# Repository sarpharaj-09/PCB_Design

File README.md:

# 🔧 PCB Design Portfolio

<p align="center">
  <strong>A collection of my PCB designs, custom footprints, and electronic hardware projects.</strong>
</p>

---

## 📌 About This Repository

Welcome to my **PCB Design Repository**!

This repository is my personal collection of printed circuit board (PCB) designs, custom footprints, and related electronic design resources. Whenever I design a new PCB, create a footprint, or work on a hardware design, I upload the relevant files here to document my progress and maintain a collection of my work.

The repository will continue to grow as I explore new electronic components, develop circuit boards, and improve my PCB design skills.

## 🎯 Repository Goals

* 📐 Store and organize my PCB designs.
* 🔩 Create and maintain custom PCB footprints.
* 🔌 Document electronic circuit and hardware projects.
* 🧩 Build a reusable collection of design resources.
* 📚 Track my progress in electronics and PCB development.
* 🚀 Share my designs and learn from the engineering community.

## 📂 What's Inside?

This repository may include the following resources as projects are developed.

| Resource            | Description                                              |
| ------------------- | -------------------------------------------------------- |
| PCB Designs         | Custom printed circuit board layouts                     |
| Footprints          | Custom component footprints for PCB layouts              |
| Schematics          | Circuit diagrams and electrical connections              |
| 3D PCB Models       | Three-dimensional board previews and component placement |
| Design Files        | Editable source files from PCB design software           |
| Manufacturing Files | Gerber files and drill files when available              |
| Documentation       | Images, notes, and project-specific information          |

*The files available for each project depend on the design and its development stage.*

## 🛠️ Tools and Technologies

My hardware design workflow may involve:

* **PCB Design Software:** KiCad, EasyEDA, or other electronic design automation (EDA) tools.
* **Circuit Design:** Schematic capture and component selection.
* **Footprint Design:** Creating and modifying component land patterns.
* **PCB Layout:** Component placement, copper routing, and board organization.
* **3D Visualization:** Inspecting board layouts and component placement.

The specific software used for each design depends on the project.

## 🗂️ Project Collection

This repository contains individual PCB design projects and related resources.

### Current Projects

* [ESP32-WROOM-32 Development Board](./ESPWROOM32_dev/) — Custom development board PCB design.

More projects, footprints, and design resources will be added as I create them.

## 🔍 How to Explore the Repository

1. Browse the project folders.
2. Open the available schematic and PCB layout files using compatible EDA software.
3. Review the included images and 3D renders, if available.
4. Inspect custom footprints and their dimensions before using them in another design.
5. Check for manufacturing files if you intend to fabricate a board.

## 📐 PCB Design Workflow

My general PCB design workflow includes:

1. **Planning** — Identify the circuit requirements and select components.
2. **Schematic Design** — Create the circuit diagram and establish electrical connections.
3. **Footprint Creation** — Create or verify component footprints against datasheets.
4. **PCB Layout** — Arrange components and route the electrical connections.
5. **Design Verification** — Review dimensions, clearances, connectivity, and design-rule-check results.
6. **3D Inspection** — Inspect component placement and mechanical alignment.
7. **Manufacturing Preparation** — Generate fabrication outputs when the design is ready.

Not every project will have completed all these stages.

## ⚠️ Important Notes

* Always verify footprint dimensions and pin assignments against the manufacturer's datasheet.
* Review the schematic and PCB design before manufacturing.
* Do not assume a design has been physically tested unless its documentation explicitly confirms it.
* Manufacturing files may not be available for every project.
* Check the applicable license and attribution requirements before reusing or redistributing design files.

## 🔮 Future Plans

As this repository grows, I plan to:

* Add more custom PCB designs.
* Develop reusable footprints for electronic components.
* Include more schematic diagrams and 3D PCB renders.
* Document component selection and design decisions.
* Add Gerber files and bills of materials where appropriate.
* Improve project organization and documentation.

## 🤝 Feedback and Contributions

Feedback, suggestions, and technical discussions are welcome.

If you find an issue with a design or have suggestions for improvement, feel free to open a GitHub issue. Contributions and constructive feedback can help improve the quality and usability of these designs.

## 👨‍💻 Author

**Sarpharaj**

* GitHub: [@sarpharaj-09](https://github.com/sarpharaj-09)
* Repository: [PCB_Design](https://github.com/sarpharaj-09/PCB_Design)

## 📄 License

Unless a license is specified in the repository, the designs should not be assumed to be available for unrestricted reuse or redistribution. A suitable license can be added to clarify the permissions for using and modifying the hardware designs.

---

<p align="center">
  <strong>Design. Build. Learn. Improve.</strong>
</p>

<p align="center">
  <i>A growing collection of my PCB designs and footprint development work.</i>
</p>

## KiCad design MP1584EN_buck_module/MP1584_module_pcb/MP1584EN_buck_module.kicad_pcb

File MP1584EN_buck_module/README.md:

# MP1584EN Adjustable Buck Converter

An adjustable DC-DC step-down converter PCB based on the MP1584EN switching regulator. The design includes input and output terminals, an adjustable output-voltage control, and a compact layout.

## Design specifications

The schematic lists the following design targets:

| Parameter | Design target |
| --- | --- |
| Regulator | MP1584EN |
| Input voltage | 4.5 V to 28 V |
| Adjustable output voltage | 0.8 V to 25 V |
| Output current | Up to 3 A, subject to input/output conditions and thermal limits |
| Output adjustment | RV1 potentiometer |

These are schematic specifications, not verified performance measurements. Check the regulator datasheet and validate the assembled board under your intended load before use.

## Board views

### Front

### Back

### Copper footprint views

| Front copper | Back copper |
| --- | --- |
|  |  |

The board is marked with input (`IN+`, `IN-`) and output (`OUT+`, `OUT-`) connections.

## Schematic

The output can be made fixed by removing potentiometer RV1 and installing a resistor at R5. The schematic gives the relationship:

```text
R5 (kΩ) = 50.25 × (VOUT - 0.8)
```

Confirm the resulting voltage and resistor value against the schematic and regulator datasheet before powering the board.

## Project files

| Path | Description |
| --- | --- |
| `MP1584_module_pcb/MP1584EN_buck_module.kicad_sch` | Editable circuit schematic |
| `MP1584_module_pcb/MP1584EN_buck_module.kicad_pcb` | Editable PCB layout |
| `MP1584_module_pcb/MP1584EN_buck_module.kicad_pro` | KiCad project settings |
| `MP1584_module_pcb/Gerber_file/` | Gerber fabrication layers |
| `media/image/` | Board renders, schematic image, and footprint views |

Open the KiCad project in a compatible KiCad version to inspect or edit the design. Review the schematic, board layout, footprints, clearances, and design-rule-check results before fabrication. The included Gerber files should also be checked against the final PCB layout.

## Safety and use

This design can involve potentially high currents. Use a suitable current-limited power source, verify input polarity and output voltage before connecting a load, and account for regulator and component heating. No assembled-board testing is documented here.

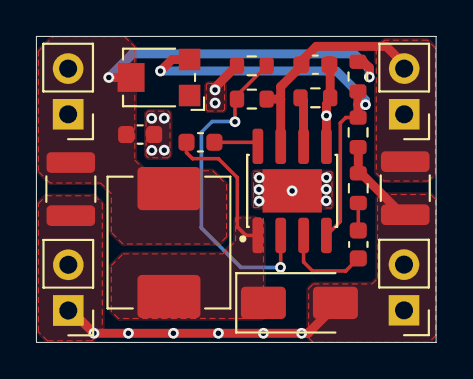
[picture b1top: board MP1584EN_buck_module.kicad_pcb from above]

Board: 2 copper layers, 22.2 x 17.0 mm, 20 parts (0 on the bottom side), 10 nets.

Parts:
C1: 10uF 50V; C_1210_3225Metric
C2, C3, C5: 100nF; C_0603_1608Metric
C4: 100pF; C_0603_1608Metric
C6: 22uF 50V; C_1210_3225Metric
D1: D; D_SMA
IN+1: TestPoint; PinHeader_1x02_P2.54mm_Vertical
IN-1: TestPoint; PinHeader_1x02_P2.54mm_Vertical
L1: 15uH; L_TechFuse_SL0630
OUT+1: TestPoint; PinHeader_1x02_P2.54mm_Vertical
OUT-1: TestPoint; PinHeader_1x02_P2.54mm_Vertical
R1, R3, R4: 100K; R_0603_1608Metric
R2: 24.9K; R_0603_1608Metric
R5: 261K(For Vout=6V); R_0603_1608Metric
R6: 40.2K; R_0603_1608Metric
RV1: R_Potentiometer; Potentiometer_Bourns_TC33X_Vertical
U1: MP1584EN; SOIC127P600X170-9N

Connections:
FB: R5.1 (A), R6.1, RV1.3, U1.4 (FB)
GND: C1.2, C2.2, C5.2, C6.2, D1.2 (A), IN-1.1 (1_1), IN-1.2, OUT-1.1 (1_1), OUT-1.2, R2.2, R3.2, R4.2, R6.2, U1.5 (GND), U1.9 (GND)
unnamed: C4.2, R4.1
unnamed: C3.1, D1.1 (K), L1.1, U1.1 (SW)
unnamed: C5.1, C6.1, L1.2, OUT+1.1 (1_1), OUT+1.2, R5.2 (B), RV1.2
unnamed: C3.2, U1.8 (BST)
unnamed: C4.1, U1.3 (COMP)
unnamed: R1.2, R2.1, U1.2 (EN)
unnamed: R3.1, U1.6 (FREQ)
unnamed: C1.1, C2.1, IN+1.1 (1_1), IN+1.2, R1.1, U1.7 (VIN)

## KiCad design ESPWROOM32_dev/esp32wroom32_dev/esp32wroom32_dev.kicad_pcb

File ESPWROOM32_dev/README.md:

# ESP32-WROOM-32 Development Board — PCB Design

<p align="center">
  <strong>Custom PCB Design for Embedded Systems and IoT Applications</strong>
</p>

---

## 📌 Overview

This project presents a custom-designed **ESP32-WROOM-32 development board PCB** for embedded systems, electronics prototyping, and Internet of Things (IoT) applications.

The project includes PCB design visualizations, the circuit schematic, and a video demonstration. The board is designed around the ESP32-WROOM-32 module, which provides wireless connectivity and processing capabilities for a wide range of embedded applications.

This repository serves as a reference for understanding, reviewing, and further developing the PCB design.

## ✨ Features

* ESP32-WROOM-32-based development board.
* Wi-Fi and Bluetooth connectivity supported by the ESP32 module.
* Custom printed circuit board (PCB) layout.
* Circuit schematic for reviewing electrical connections.
* 3D PCB visualization for inspecting component placement.
* PCB design suitable for embedded systems and IoT prototyping.
* Design assets organized for convenient reference.

*Note: Actual board interfaces, power circuitry, and supported peripherals depend on the implemented schematic and component selection.*

---

## 📸 PCB Design Gallery

### 1. 3D Front View

The 3D front view provides a visual representation of the PCB and its component placement.

### 2. 3D Back View

The back view helps inspect the reverse side of the PCB and its layout.

### 3. PCB Layout

The PCB layout illustrates the board design, component arrangement, and routing.

### 4. Circuit Schematic

The schematic provides an overview of the circuit connections and electronic components.

---

## 🎥 Project Video Demonstration

Watch the PCB design demonstration to see the board visualization and design presentation.

<p align="center">
  
</p>

<p align="center">
  <a href="./media/videos/pcb_design_demo.mp4">
    <strong>▶️ Watch the PCB Design Demo</strong>
  </a>
</p>

**Video location:** [`media/videos/pcb_design_demo.mp4`](./media/videos/pcb_design_demo.mp4)

*Click the thumbnail or the link above to open the video.*

---

## 🛠️ Hardware and Design Tools

| Item                   | Description                         |
| ---------------------- | ----------------------------------- |
| Microcontroller module | ESP32-WROOM-32                      |
| Hardware type          | Custom PCB development board        |
| Design documentation   | PCB layout and circuit schematic    |
| Visualization          | 3D PCB renders                      |
| Main application       | Embedded systems and IoT            |
| Design software        | Refer to the original project files |

The PCB design software and additional hardware specifications should be documented according to the actual project files.

---

## 📂 Repository Structure

The project media files are organized as follows:

```text
ESPWROOM32_dev/
├── README.md
└── media/
    ├── images/
    │   ├── pcb_3d_front.png
    │   ├── pcb_3d_back.png
    │   ├── pcb_layout.png
    │   ├── schematic.png
    │   └── video_thumbnail.png
    └── videos/
        └── pcb_design_demo.mp4
```

### File Descriptions

| File                  | Purpose                                          |
| --------------------- | ------------------------------------------------ |
| `pcb_3d_front.png`    | Front-side 3D PCB visualization                  |
| `pcb_3d_back.png`     | Back-side 3D PCB visualization                   |
| `pcb_layout.png`      | PCB layout and routing view                      |
| `schematic.png`       | Circuit schematic                                |
| `video_thumbnail.png` | Preview image linking to the demonstration video |
| `pcb_design_demo.mp4` | PCB design demonstration video                   |

---

## 🚀 Getting Started

### 1. Clone the Repository

Open a terminal and run:

```bash
git clone https://github.com/sarpharaj-09/PCB_Design.git
```

### 2. Navigate to the Project Directory

```bash
cd PCB_Design/ESPWROOM32_dev
```

### 3. Review the Design

* Open the images to inspect the PCB and schematic.
* Watch the demonstration video.
* Review the original schematic and PCB design files, if included in the repository.

### 4. Modify or Manufacture the PCB

If the editable design files are available, open them in the compatible PCB design software to inspect or modify the board.

Before manufacturing, verify the schematic, footprints, board dimensions, electrical clearances, routing, and design-rule-check results. Generate the required fabrication files using the appropriate design software.

---

## 💡 Potential Applications

The ESP32-WROOM-32 platform is suitable for projects such as:

* Internet of Things (IoT) devices.
* Wireless sensor monitoring.
* Home automation systems.
* Remote monitoring and control.
* Embedded systems prototyping.
* Wi-Fi and Bluetooth-enabled electronics.
* Educational electronics and PCB design projects.

These are potential applications of the platform, not necessarily implemented or tested features of this specific board.

---

## 🔍 Future Improvements

Possible future improvements to the project include:

* Adding detailed component specifications and a bill of materials (BOM).
* Including the editable schematic and PCB source files.
* Providing Gerber and drill files for fabrication.
* Documenting the power supply and USB programming interface, if implemented.
* Adding board dimensions and connector pinout diagrams.
* Including hardware testing results and assembly instructions.
* Providing a demonstration of the assembled board.

---

## 🤝 Contributions

Suggestions and improvements are welcome.

To contribute:

1. Fork this repository.
2. Create a branch for your changes.
3. Make and commit your modifications.
4. Submit a pull request with a description of the improvements.

---

## 📄 License

Please check the repository's license file for the applicable usage and redistribution terms.

If no license is included, the project should not be assumed to be open for unrestricted reuse or redistribution. Consider adding an appropriate license if you intend to share the design for reuse.

---

## 👨‍💻 Author

**Sarpharaj**

GitHub: [@sarpharaj-09](https://github.com/sarpharaj-09)

Project: [PCB_Design — ESPWROOM32_dev](https://github.com/sarpharaj-09/PCB_Design/tree/main/ESPWROOM32_dev)

---

<p align="center">
  <strong>Designed for embedded systems, electronics prototyping, and IoT development.</strong>
</p>

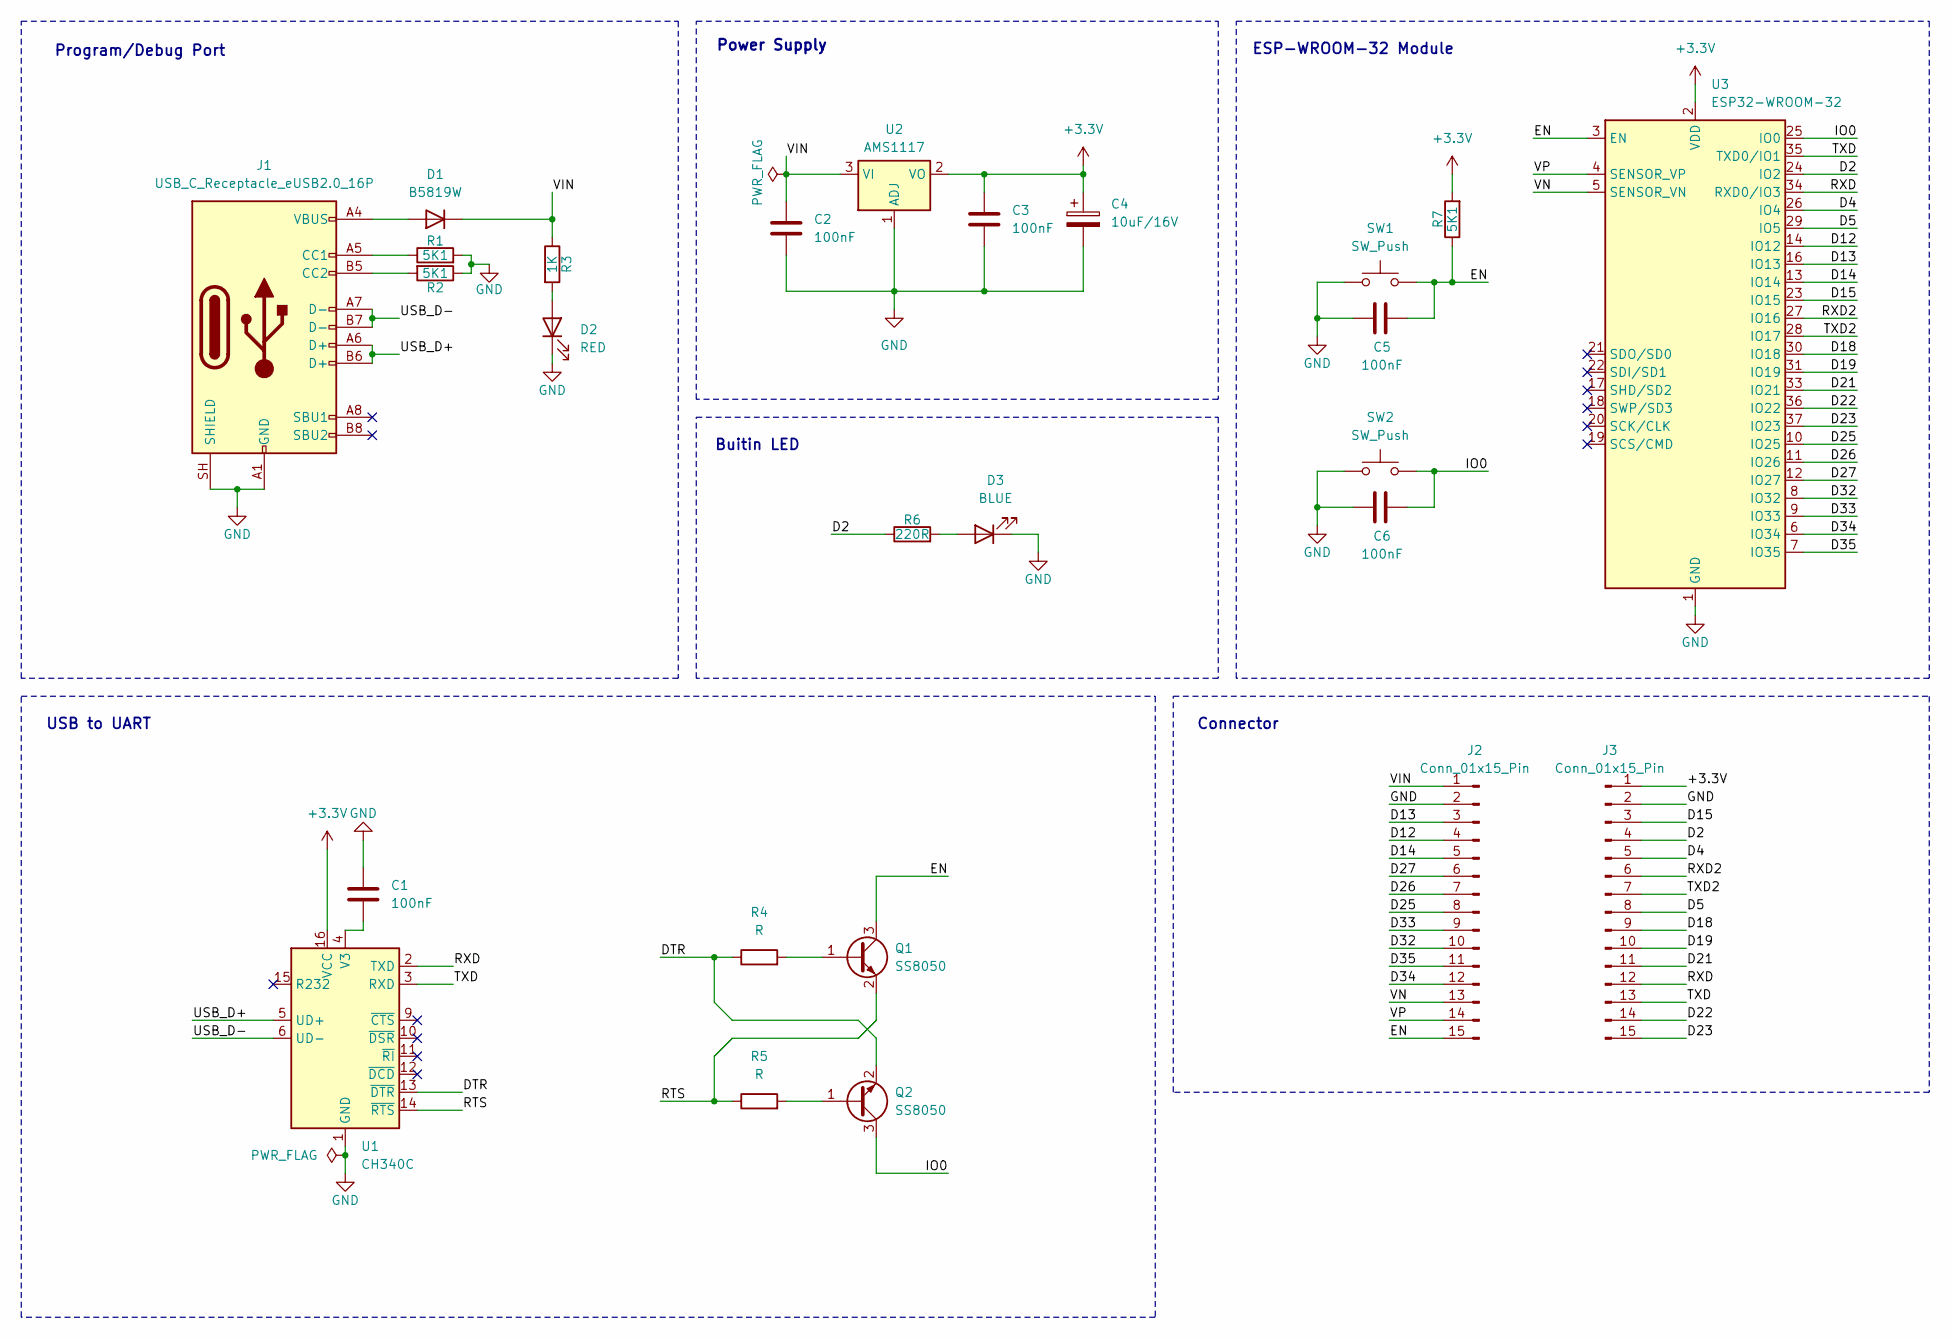
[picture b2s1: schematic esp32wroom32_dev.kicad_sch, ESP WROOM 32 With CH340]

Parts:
C1, C2, C3, C5, C6: 100nF; C_0603_1608Metric
C4: 10uF/16V; CP_EIA-3216-10_Kemet-I
D1: B5819W; D_SOD-123
D2: RED; LED_0603_1608Metric
D3: BLUE; LED_0603_1608Metric
J1: USB_C_Receptacle_eUSB2.0_16P; USB_C_Receptacle_HRO_TYPE-C-31-M-12
J2, J3: Conn_01x15_Pin; PinHeader_1x15_P2.54mm_Vertical
Q1, Q2: SS8050; SOT-23
R1, R2, R7: 5K1; R_0603_1608Metric
R3: 1K; R_0603_1608Metric
R4, R5: R; R_0603_1608Metric
R6: 220R; R_0603_1608Metric
SW1, SW2: SW_Push; SW_Push_SPST_NO_Alps_SKRK
U1: CH340C; SOIC-16_3.9x9.9mm_P1.27mm
U2: AMS1117; SOT-223-3_TabPin2
U3: ESP32-WROOM-32

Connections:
+3.3V: C3.1, C4.1, J3.1, R7.2, U1.16 (VCC), U2.2 (VO), U3.2 (VDD)
/D2: J3.4, R6.1, U3.24 (IO2)
/D4: J3.5, U3.26 (IO4)
/D5: J3.8, U3.29 (IO5)
/D12: J2.4, U3.14 (IO12)
/D13: J2.3, U3.16 (IO13)
/D14: J2.5, U3.13 (IO14)
/D15: J3.3, U3.23 (IO15)
/D18: J3.9, U3.30 (IO18)
/D19: J3.10, U3.31 (IO19)
/D21: J3.11, U3.33 (IO21)
/D22: J3.14, U3.36 (IO22)
/D23: J3.15, U3.37 (IO23)
/D25: J2.8, U3.10 (IO25)
/D26: J2.7, U3.11 (IO26)
/D27: J2.6, U3.12 (IO27)
/D32: J2.10, U3.8 (IO32)
/D33: J2.9, U3.9 (IO33)
/D34: J2.12, U3.6 (IO34)
/D35: J2.11, U3.7 (IO35)
/DTR: Q2.2 (E), R4.1, U1.13 (~DTR)
/EN: C5.2, J2.15, Q1.3 (C), R7.1, SW1.2, U3.3 (EN)
/IO0: C6.2, Q2.3 (C), SW2.2, U3.25 (IO0)
/RTS: Q1.2 (E), R5.1, U1.14 (~RTS)
/RXD: J3.12, U1.2 (TXD), U3.34 (RXD0/IO3)
/RXD2: J3.6, U3.27 (IO16)
/TXD: J3.13, U1.3 (RXD), U3.35 (TXD0/IO1)
/TXD2: J3.7, U3.28 (IO17)
/USB_D+: J1.A6 (D+), J1.B6 (D+), U1.5 (UD+)
/USB_D-: J1.A7 (D-), J1.B7 (D-), U1.6 (UD-)
/VIN: C2.1, D1.1 (K), J2.1, R3.1, U2.3 (VI)
/VN: J2.13, U3.5 (SENSOR_VN)
/VP: J2.14, U3.4 (SENSOR_VP)
GND: C1.1, C2.2, C3.2, C4.2, C5.1, C6.1, D2.1 (K), D3.1 (K), J1.A1 (GND), J1.A12 (GND), J1.B1 (GND), J1.B12 (GND), J1.SH (SHIELD), J2.2, J3.2, R1.2, R2.1, SW1.1, SW2.1, U1.1 (GND), U2.1 (ADJ), U3.1 (GND), U3.15 (GND), U3.38 (GND), U3.39 (GND)
unnamed: D1.2 (A), J1.A4 (VBUS), J1.A9 (VBUS), J1.B4 (VBUS), J1.B9 (VBUS)
unnamed: D2.2 (A), R3.2
unnamed: D3.2 (A), R6.2
unnamed: J1.A5 (CC1), R1.1
unnamed: J1.B5 (CC2), R2.2
unnamed: Q1.1 (B), R4.2
unnamed: Q2.1 (B), R5.2
unnamed: C1.2, U1.4 (V3)

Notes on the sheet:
Program/Debug Port
Connector
USB to UART
ESP-WROOM-32 Module
Buitin LED
Power Supply

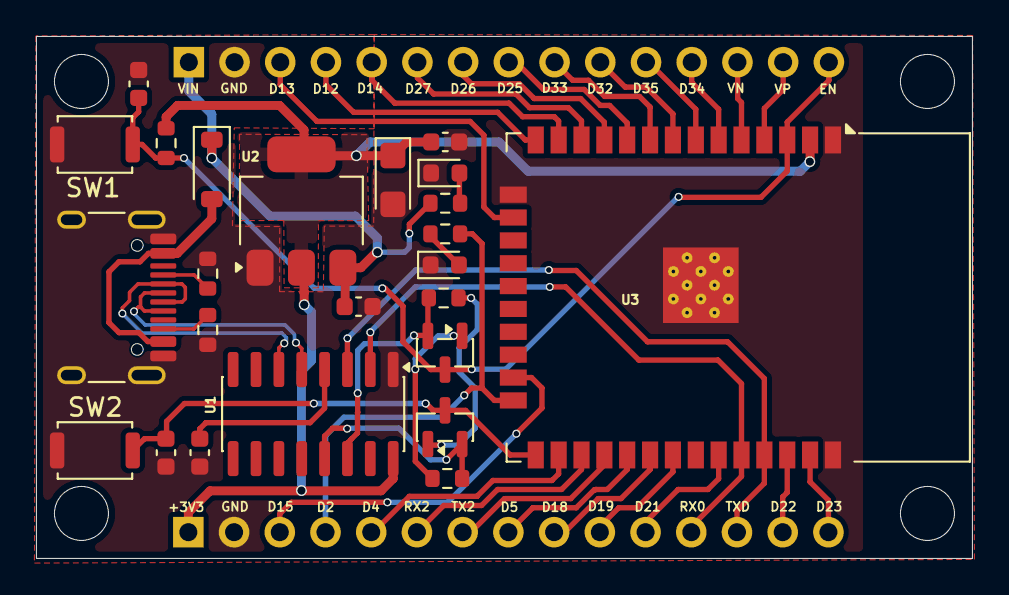
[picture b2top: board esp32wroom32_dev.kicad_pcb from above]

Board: 2 copper layers, 52.0 x 29.0 mm, 26 parts (0 on the bottom side), 42 nets.

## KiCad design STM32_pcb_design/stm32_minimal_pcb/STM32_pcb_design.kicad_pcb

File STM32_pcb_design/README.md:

# ESP32-WROOM-32 Development Board — PCB Design

<p align="center">
  <strong>Custom PCB Design for Embedded Systems and IoT Applications</strong>
</p>

---

## 📌 Overview

This project presents a custom-designed **ESP32-WROOM-32 development board PCB** for embedded systems, electronics prototyping, and Internet of Things (IoT) applications.

The project includes PCB design visualizations, the circuit schematic, and a video demonstration. The board is designed around the ESP32-WROOM-32 module, which provides wireless connectivity and processing capabilities for a wide range of embedded applications.

This repository serves as a reference for understanding, reviewing, and further developing the PCB design.

## ✨ Features

* ESP32-WROOM-32-based development board.
* Wi-Fi and Bluetooth connectivity supported by the ESP32 module.
* Custom printed circuit board (PCB) layout.
* Circuit schematic for reviewing electrical connections.
* 3D PCB visualization for inspecting component placement.
* PCB design suitable for embedded systems and IoT prototyping.
* Design assets organized for convenient reference.

*Note: Actual board interfaces, power circuitry, and supported peripherals depend on the implemented schematic and component selection.*

---

## 📸 PCB Design Gallery

### 1. 3D Front View

The 3D front view provides a visual representation of the PCB and its component placement.

### 2. 3D Back View

The back view helps inspect the reverse side of the PCB and its layout.

### 3. PCB Layout

The PCB layout illustrates the board design, component arrangement, and routing.

### 4. Circuit Schematic

The schematic provides an overview of the circuit connections and electronic components.

---

## 🎥 Project Video Demonstration

Watch the PCB design demonstration to see the board visualization and design presentation.

<p align="center">
  <a href="./media/videos/pcb_design_demo.mp4">
    ▶️ <strong>Watch the PCB Design Demo (MP4)</strong>
  </a>
</p>

**Video location:** [`media/videos/pcb_design_demo.mp4`](./media/videos/pcb_design_demo.mp4)

*Click the link above to open the video.*

---

## 🛠️ Hardware and Design Tools

| Item                   | Description                         |
| ---------------------- | ----------------------------------- |
| Microcontroller module | ESP32-WROOM-32                      |
| Hardware type          | Custom PCB development board        |
| Design documentation   | PCB layout and circuit schematic    |
| Visualization          | 3D PCB renders                      |
| Main application       | Embedded systems and IoT            |
| Design software        | Refer to the original project files |

The PCB design software and additional hardware specifications should be documented according to the actual project files.

---

## 📂 Repository Structure

The project media files are organized as follows:

```text
ESPWROOM32_dev/
├── README.md
└── media/
    ├── images/
    │   ├── pcb_3d_front.png
    │   ├── pcb_3d_back.png
    │   ├── pcb_layout.png
    │   └── schematic.png
    └── videos/
        └── pcb_design_demo.mp4
```

### File Descriptions

| File                  | Purpose                         |
| --------------------- | ------------------------------- |
| `pcb_3d_front.png`    | Front-side 3D PCB visualization |
| `pcb_3d_back.png`     | Back-side 3D PCB visualization  |
| `pcb_layout.png`      | PCB layout and routing view     |
| `schematic.png`       | Circuit schematic               |
| `pcb_design_demo.mp4` | PCB design demonstration video  |

---

## 🚀 Getting Started

### 1. Clone the Repository

Open a terminal and run:

```bash
git clone https://github.com/sarpharaj-09/PCB_Design.git
```

### 2. Navigate to the Project Directory

```bash
cd PCB_Design/ESPWROOM32_dev
```

### 3. Review the Design

* Open the images to inspect the PCB and schematic.
* Watch the demonstration video.
* Review the original schematic and PCB design files, if included in the repository.

### 4. Modify or Manufacture the PCB

If the editable design files are available, open them in the compatible PCB design software to inspect or modify the board.

Before manufacturing, verify the schematic, footprints, board dimensions, electrical clearances, routing, and design-rule-check results. Generate the required fabrication files using the appropriate design software.

---

## 💡 Potential Applications

The ESP32-WROOM-32 platform is suitable for projects such as:

* Internet of Things (IoT) devices.
* Wireless sensor monitoring.
* Home automation systems.
* Remote monitoring and control.
* Embedded systems prototyping.
* Wi-Fi and Bluetooth-enabled electronics.
* Educational electronics and PCB design projects.

These are potential applications of the platform, not necessarily implemented or tested features of this specific board.

---

## 🔍 Future Improvements

Possible future improvements to the project include:

* Adding detailed component specifications and a bill of materials (BOM).
* Including the editable schematic and PCB source files.
* Providing Gerber and drill files for fabrication.
* Documenting the power supply and USB programming interface, if implemented.
* Adding board dimensions and connector pinout diagrams.
* Including hardware testing results and assembly instructions.
* Providing a demonstration of the assembled board.

---

## 🤝 Contributions

Suggestions and improvements are welcome.

To contribute:

1. Fork this repository.
2. Create a branch for your changes.
3. Make and commit your modifications.
4. Submit a pull request with a description of the improvements.

---

## 📄 License

Please check the repository's license file for the applicable usage and redistribution terms.

If no license is included, the project should not be assumed to be open for unrestricted reuse or redistribution. Consider adding an appropriate license if you intend to share the design for reuse.

---

## 👨‍💻 Author

**Sarpharaj**

GitHub: [@sarpharaj-09](https://github.com/sarpharaj-09)

Project: [PCB_Design — ESPWROOM32_dev](https://github.com/sarpharaj-09/PCB_Design/tree/main/ESPWROOM32_dev)

---

<p align="center">
  <strong>Designed for embedded systems, electronics prototyping, and IoT development.</strong>
</p>

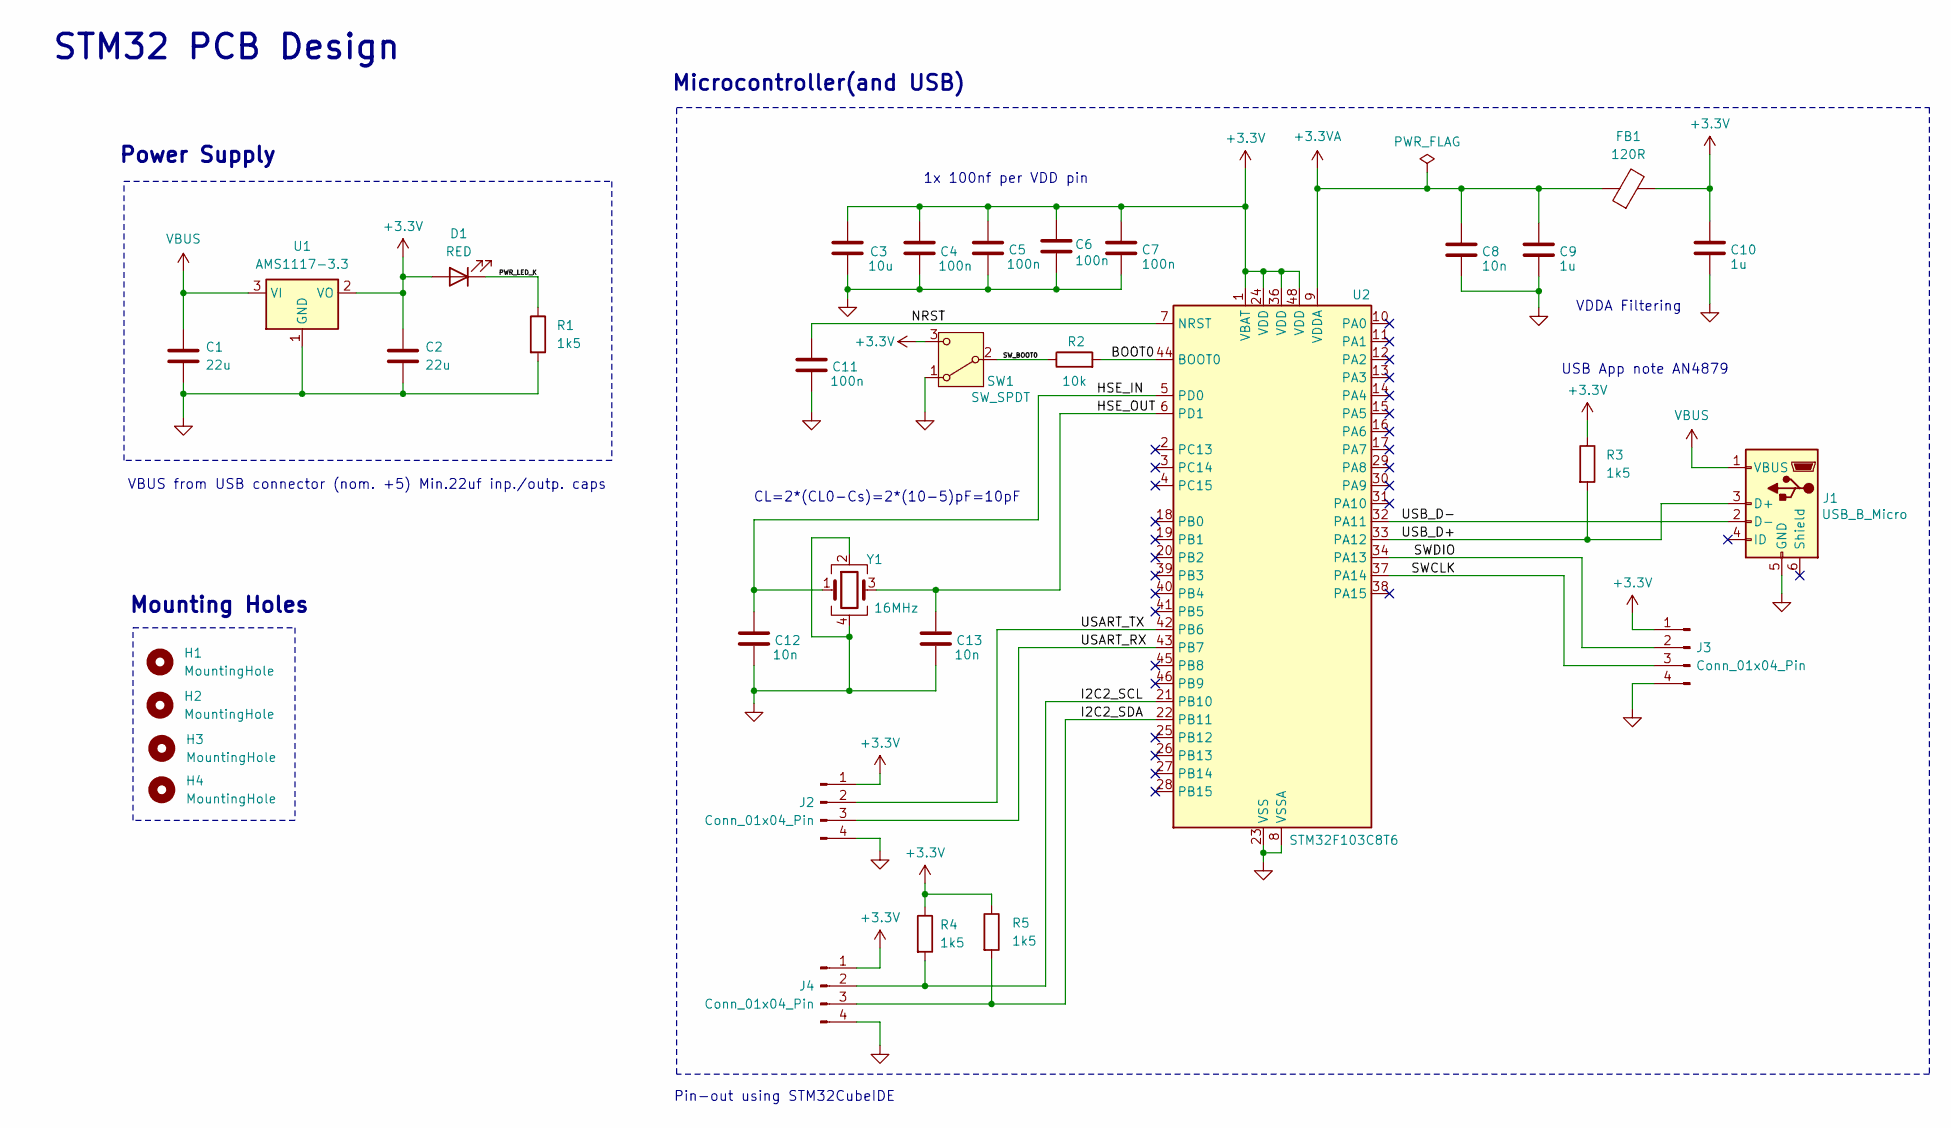
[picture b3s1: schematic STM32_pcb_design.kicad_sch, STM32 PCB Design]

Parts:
C1, C2: 22u; C_0805_2012Metric
C3: 10u; C_0603_1608Metric
C4, C5, C6, C7, C11: 100n; C_0402_1005Metric
C8, C12, C13: 10n; C_0402_1005Metric
C9, C10: 1u; C_0402_1005Metric
D1: RED; LED_0603_1608Metric
FB1: 120R; L_0603_1608Metric
H1, H2, H3, H4: MountingHole; MountingHole_2.2mm_M2
J1: USB_B_Micro; USB_Micro-B_Wuerth_629105150521
J2, J3, J4: Conn_01x04_Pin; PinHeader_1x04_P2.54mm_Vertical
R1, R3, R4, R5: 1k5; R_0402_1005Metric
R2: 10k; R_0402_1005Metric
SW1: SW_SPDT; SW_SPDT_PCM12
U1: AMS1117-3.3; SOT-223-3_TabPin2
U2: STM32F103C8T6; LQFP-48_7x7mm_P0.5mm
Y1: 16MHz; Crystal_SMD_3225-4Pin_3.2x2.5mm

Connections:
+3.3V: C2.1, C3.1, C4.1, C5.1, C6.1, C7.1, C10.1, D1.2 (A), FB1.2, J2.1, J3.1, J4.1, R3.1, R4.1, R5.1, SW1.3 (C), U1.2 (VO), U2.1 (VBAT), U2.24 (VDD), U2.36 (VDD), U2.48 (VDD)
+3.3VA: C8.1, C9.1, FB1.1, U2.9 (VDDA)
/BOOT0: R2.2, U2.44 (BOOT0)
/HSE_IN: C12.1, U2.5 (PD0), Y1.1
/HSE_OUT: C13.1, U2.6 (PD1), Y1.3
/I2C2_SCL: J4.2, R4.2, U2.21 (PB10)
/I2C2_SDA: J4.3, R5.2, U2.22 (PB11)
/NRST: C11.1, U2.7 (NRST)
/PWR_LED_K: D1.1 (K), R1.1
/SWCLK: J3.3, U2.37 (PA14)
/SWDIO: J3.2, U2.34 (PA13)
/SW_BOOT0: R2.1, SW1.2 (B)
/USART_RX: J2.3, U2.43 (PB7)
/USART_TX: J2.2, U2.42 (PB6)
/USB_D+: J1.3 (D+), R3.2, U2.33 (PA12)
/USB_D-: J1.2 (D-), U2.32 (PA11)
GND: C1.2, C2.2, C3.2, C4.2, C5.2, C6.2, C7.2, C8.2, C9.2, C10.2, C11.2, C12.2, C13.2, J1.5 (GND), J2.4, J3.4, J4.4, R1.2, SW1.1 (A), U1.1 (GND), U2.8 (VSSA), U2.23 (VSS), U2.35 (VSS), U2.47 (VSS), Y1.2, Y1.4
VBUS: C1.1, J1.1 (VBUS), U1.3 (VI)

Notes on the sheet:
VBUS from USB connector (nom. +5) Min.22uf inp./outp. caps
1x 100nf per VDD pin
CL=2*(CL0-Cs)=2*(10-5)pF=10pF
STM32 PCB Design
Power Supply
VDDA Filtering
USB App note AN4879
Microcontroller(and USB)
Pin-out using STM32CubeIDE
Mounting Holes

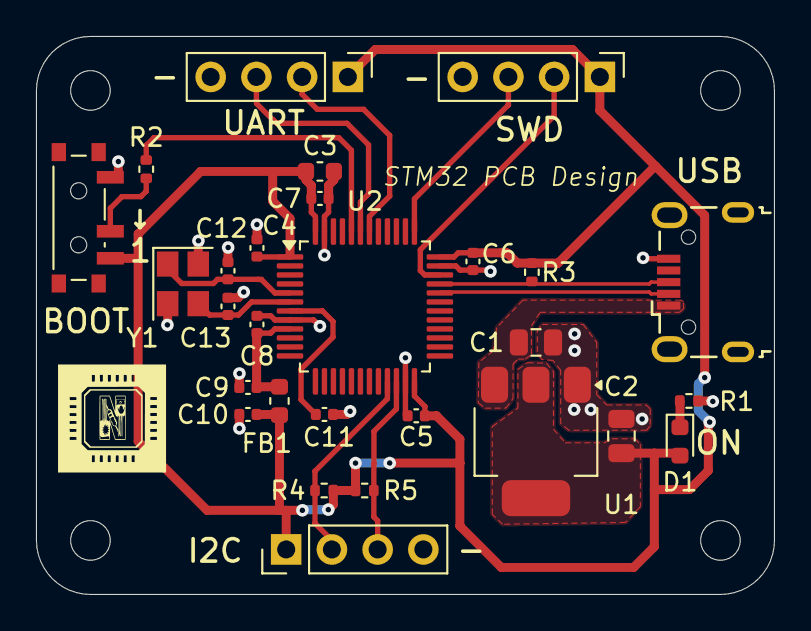
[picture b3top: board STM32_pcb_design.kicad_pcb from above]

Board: 2 copper layers, 41.0 x 31.0 mm, 32 parts (0 on the bottom side), 18 nets.
